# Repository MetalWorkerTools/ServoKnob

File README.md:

# ServoKnob
A PWM controlled RC servo that rotates a potentiometer to set a motor speed by CNC control.
A small micro controller (ESP32-C3) monitors the PWM signal from a CNC controller. It positions a RC servo depending on the PWM duty cylcle. The RC servo turns the knob that controls the motor speed. Doing so, "any" motor witch speed is controlled by a knob can be controlled by a CNC controller. The micro controller has a OLED display and a rotary knob to control the motor speed manually and configure settings. For easy connection, there is a PCB designed using Eagle. You can also wire wrap the whole system. A Visual Studio Code project contains the firmware that is written in C++.
## this page is under construction

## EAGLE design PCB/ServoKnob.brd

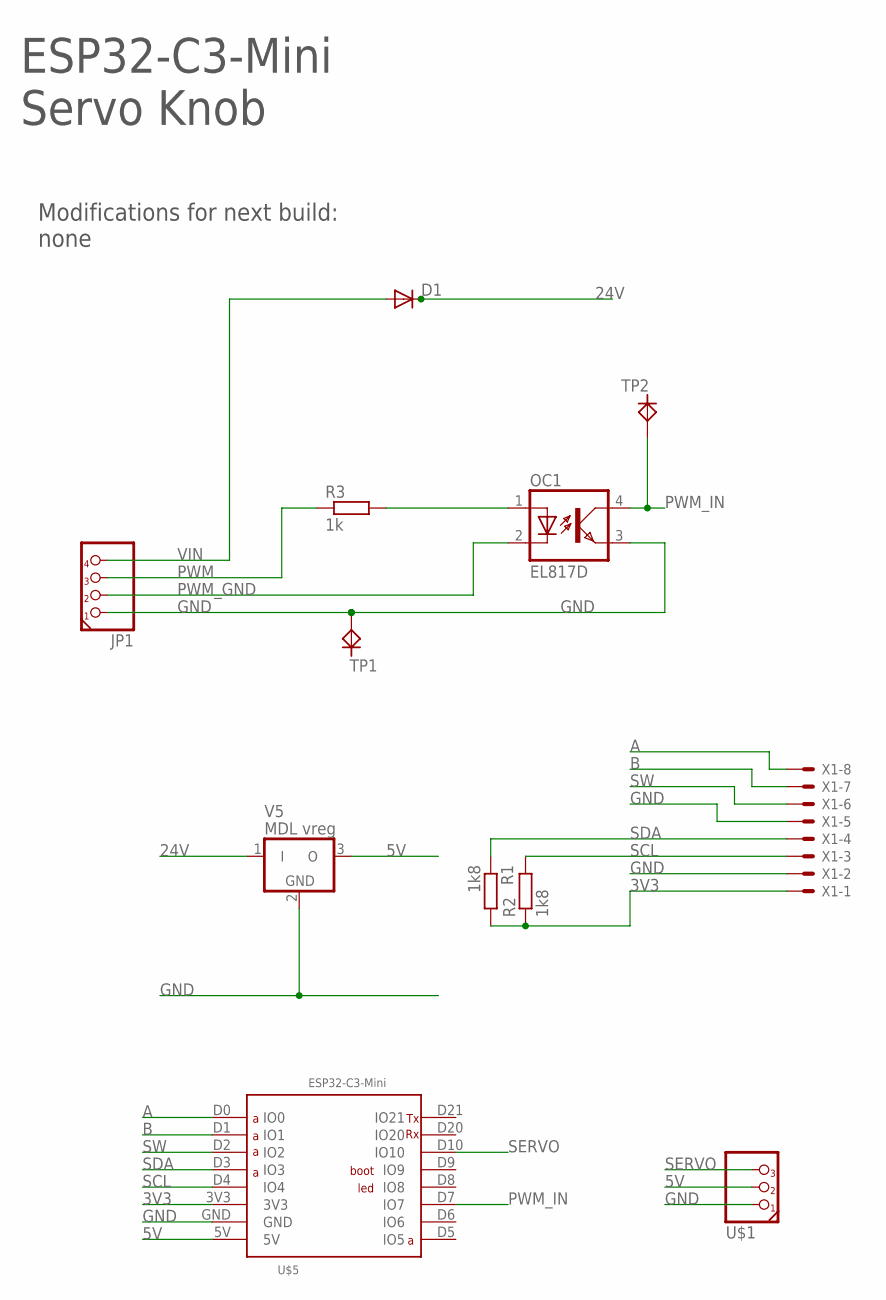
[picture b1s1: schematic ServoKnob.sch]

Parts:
D1: DIODE-DO214ACI; DO214ACI
JP1: PINHD-1X4PH254; 1X04/PH254
OC1: EL817D; DIL04
R1, R2: 1k8; R0805
R3: 1k; R0805
TP1, TP2: TESTPIN-TP10; TP10
U$1: PINHD-1X3; 1X03
U$5: ESP32C3MINIL; ESP32-C3-MINI
V5: MDL vreg; MDLSTEPDOWNV02H
X1: JST-XH-08-PIN-L; JST-XH-08-L

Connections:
3V3: R1.2, R2.1, U$5.3V3, X1.1
5V: U$1.2, U$5.5V, V5.3 (O)
24V: D1.C, V5.1 (I)
A: U$5.D0 (IO0), X1.8
B: U$5.D1 (IO1), X1.7
GND: JP1.1, OC1.3 (EMIT), TP1.TP, U$1.1, U$5.GND, V5.2 (GND), X1.2, X1.5
unnamed: OC1.1 (A), R3.2
PWM: JP1.3, R3.1
PWM_GND: JP1.2, OC1.2 (C)
PWM_IN: OC1.4 (COL), TP2.TP, U$5.D7 (IO7)
SCL: R2.2, U$5.D4 (IO4), X1.3
SDA: R1.1, U$5.D3 (IO3), X1.4
SERVO: U$1.3, U$5.D10 (IO10)
SW: U$5.D2 (IO2), X1.6
VIN: D1.A, JP1.4

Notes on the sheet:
ESP32-C3-Mini Servo Knob
Modifications for next build: none

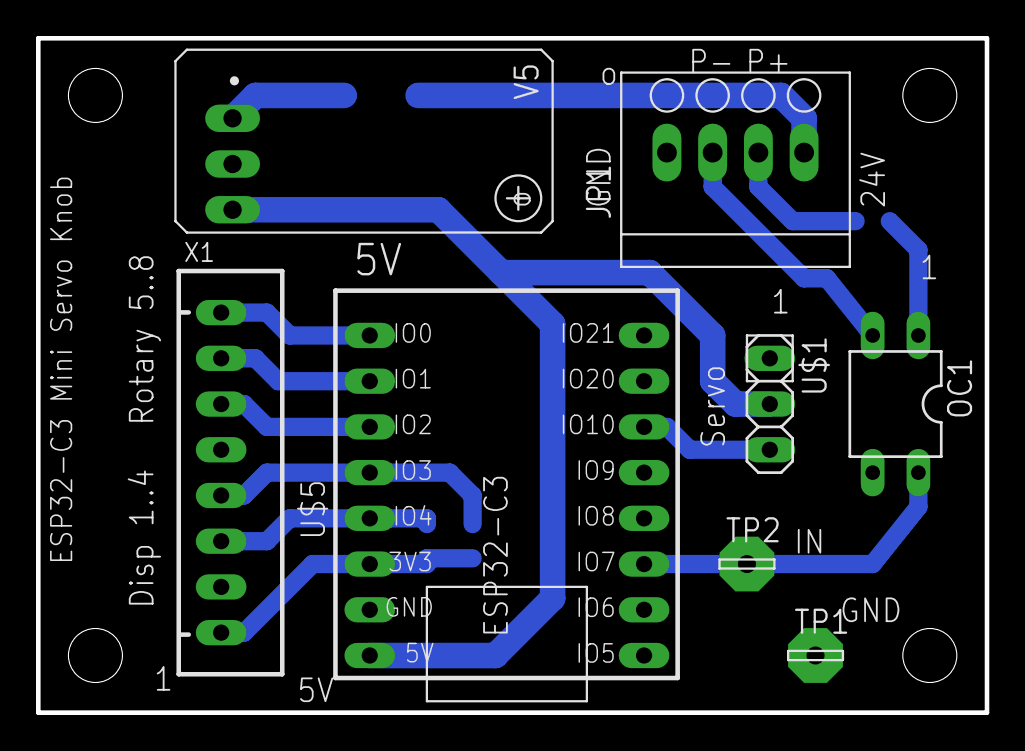
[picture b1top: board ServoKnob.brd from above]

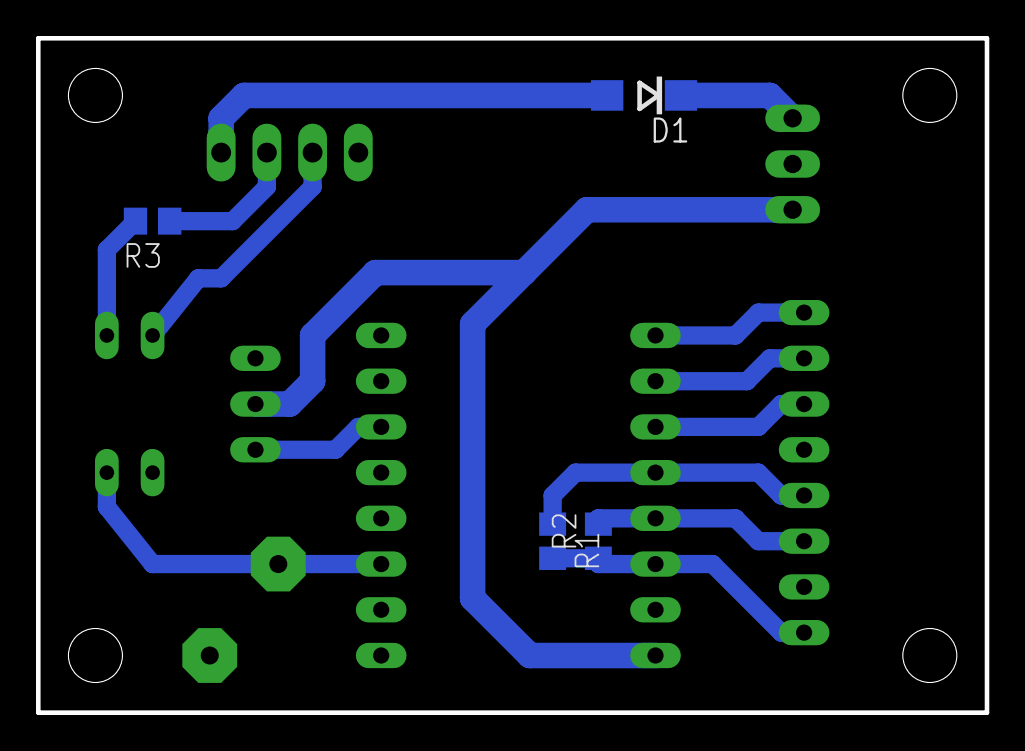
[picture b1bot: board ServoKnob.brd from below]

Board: 2 copper layers, 52.7 x 37.5 mm, 12 parts (4 on the bottom side), 15 nets.

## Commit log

2024-12-23 Release 1.0
    First release
2024-12-23 Cleanup
2024-12-23 Added Eagle PCB files
2024-12-25 Added PCB holder step file and firmware cleanup
    Added PCB holder step
    Cleanup Firmware
2024-12-31 Firmware update
    Firmware update
2024-12-31 Fixed not activating servo anymore after a PWM signal change
